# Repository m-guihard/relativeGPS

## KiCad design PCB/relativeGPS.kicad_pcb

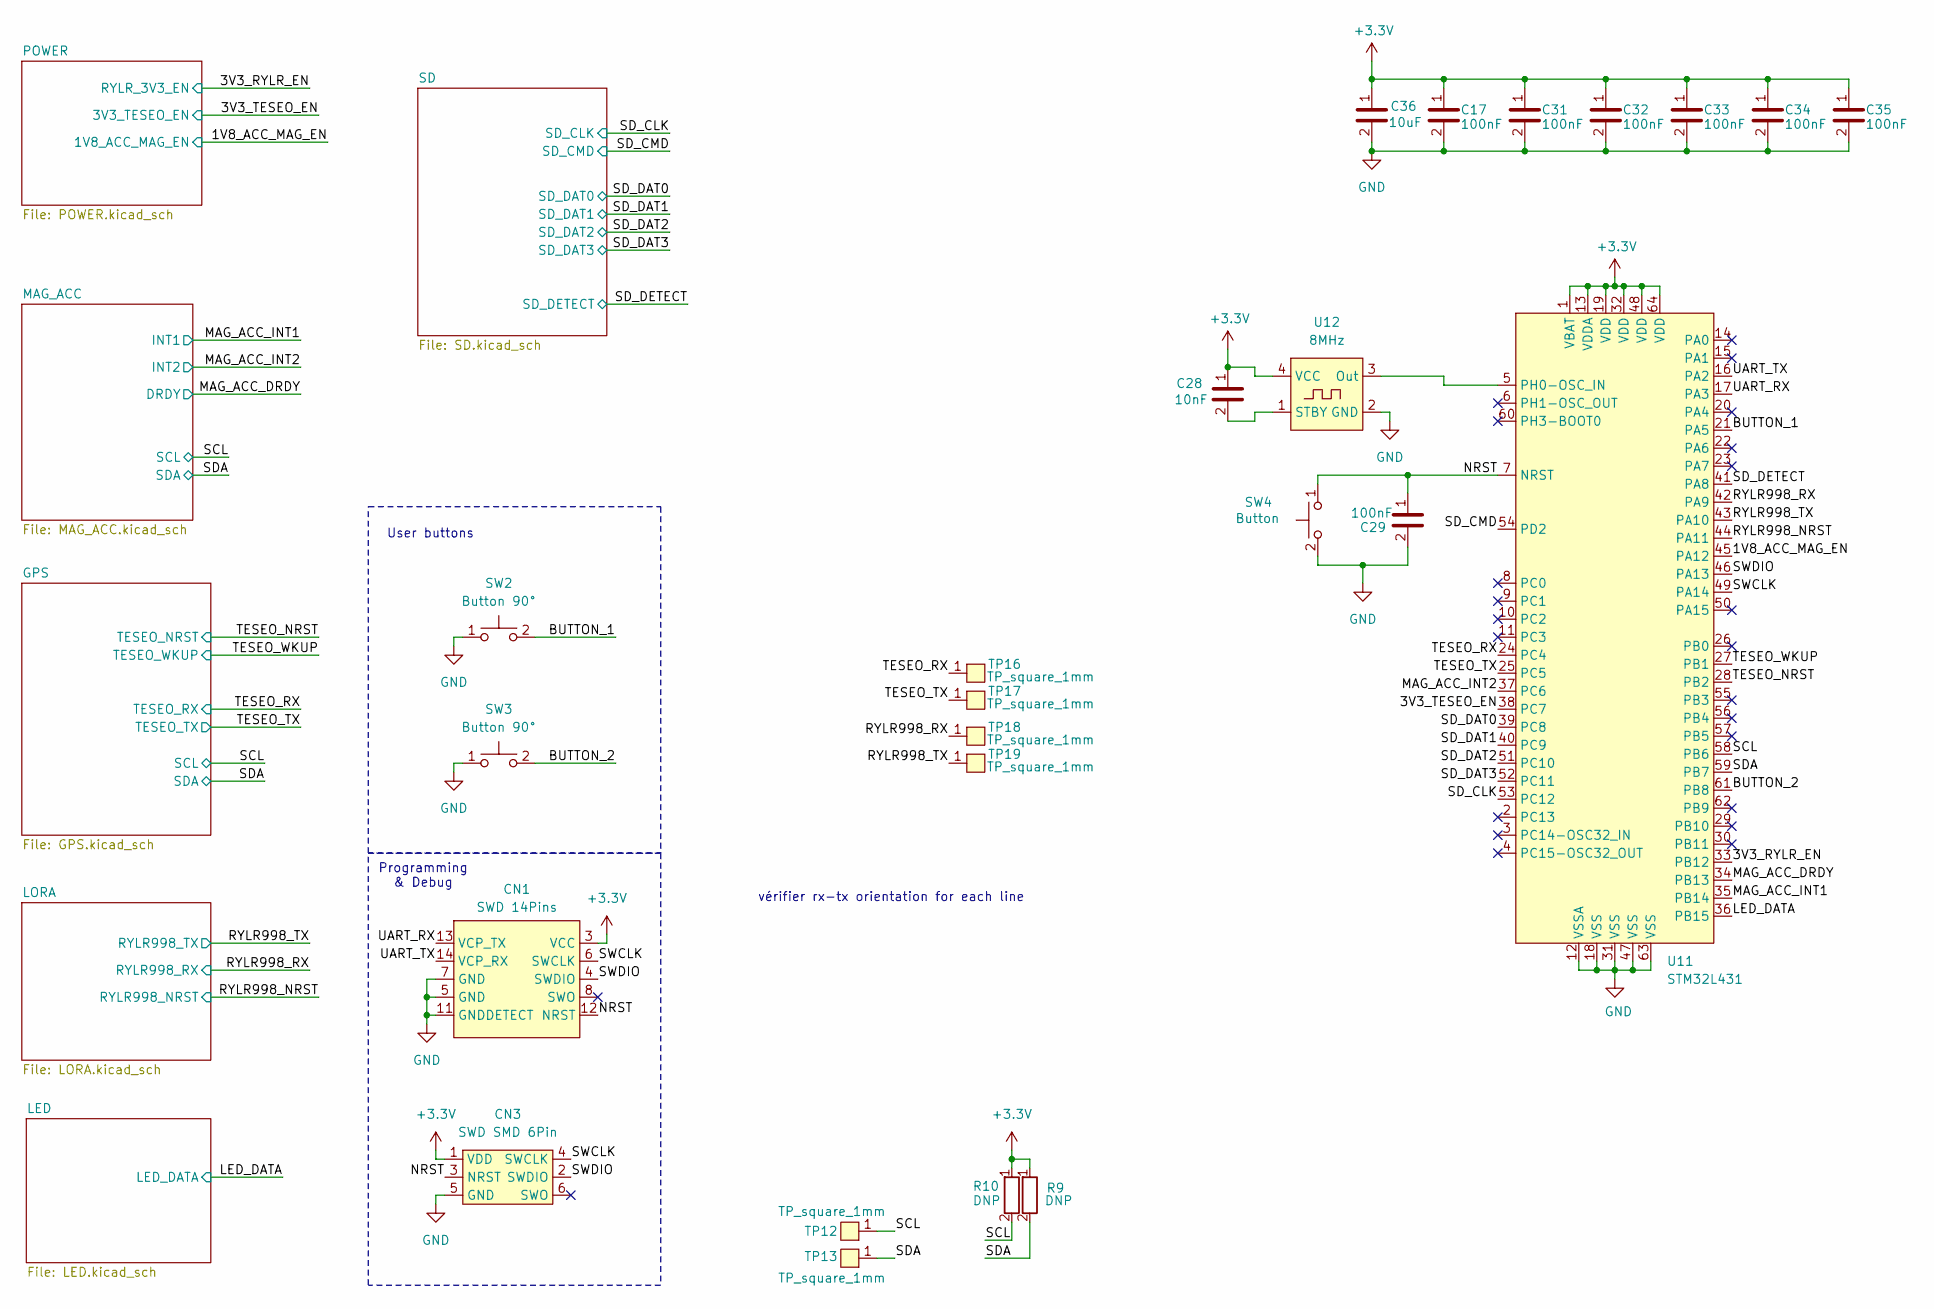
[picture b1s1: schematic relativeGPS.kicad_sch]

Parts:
C17, C29, C31, C32, C33, C34, C35: C_100nF_50V_10%_X7R_0402_H0.55; C_0402_H0.55; Manufacturer P/N GRM155R71H104KE14J; Digikey P/N 490-13342-1-ND
C28: C_10nF_50V_10%_X7R_0402_H0.55; C_0402_H0.55; Manufacturer P/N CGA2B3X7R1H103K050BE; Digikey P/N 445-173650-1-ND
C36: C_10uF_10V_20%_X5R_0402_H0.55; C_0402_H0.55; Manufacturer P/N GRM155R61A106ME11D; Digikey P/N 490-GRM155R61A106ME11DCT-ND
CN1: FTSH-107-01-L-DV-K-P-TR; Manufacturer P/N FTSH-107-01-L-DV-K-P-TR; Digikey P/N SAM13946CT-ND
CN3: TC2030-IDC; Debug_pads_6pin
R9, R10: R_DNP_0402; R_0402_H0.4
SW2, SW3: EVQ-P7A01P; Manufacturer P/N EVQ-P7A01P; Digikey P/N P16763CT-ND
SW4: TL3315NF160Q; Manufacturer P/N TL3315NF160Q; Digikey P/N EG4621CT-ND
TP12, TP13, TP16, TP17, TP18, TP19: TP_square_1mm; Testpoint_square_1mm
U11: STM32L431RCT6TR; LQFP-64_10x10mm_P0.5mm; Manufacturer P/N STM32L431RCT6TR; Digikey P/N 497-STM32L431RCT6CT-ND
U12: ASE-8.000MHZ-L-C-T; Manufacturer P/N ASE-8.000MHZ-L-C-T; Digikey P/N 535-ASE-8.000MHZ-L-C-TCT-ND

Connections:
+3.3V: C17.1, C28.1, C31.1, C32.1, C33.1, C34.1, C35.1, C36.1, CN1.3 (VCC), CN3.1 (VDD), R9.1, R10.1, U11.1 (VBAT), U11.13 (VDDA), U11.19 (VDD), U11.32 (VDD), U11.48 (VDD), U11.64 (VDD), U12.4 (VCC); also elsewhere on the board
/1V8_ACC_MAG_EN: U11.45 (PA12); also elsewhere on the board
/3V3_RYLR_EN: U11.33 (PB12); also elsewhere on the board
/3V3_TESEO_EN: U11.38 (PC7); also elsewhere on the board
/BUTTON_1: SW2.2, U11.21 (PA5)
/BUTTON_2: SW3.2, U11.61 (PB8)
/LED_DATA: U11.36 (PB15); also elsewhere on the board
/MAG_ACC_DRDY: U11.34 (PB13); also elsewhere on the board
/MAG_ACC_INT1: U11.35 (PB14); also elsewhere on the board
/MAG_ACC_INT2: U11.37 (PC6); also elsewhere on the board
/NRST: C29.1, CN1.12 (NRST), CN3.3 (NRST), SW4.1, U11.7 (NRST)
/RYLR998_NRST: U11.44 (PA11); also elsewhere on the board
/RYLR998_RX: TP18.1, U11.42 (PA9); also elsewhere on the board
/RYLR998_TX: TP19.1, U11.43 (PA10); also elsewhere on the board
/SCL: R10.2, TP12.1, U11.58 (PB6); also elsewhere on the board
/SDA: R9.2, TP13.1, U11.59 (PB7); also elsewhere on the board
/SD_CLK: U11.53 (PC12); also elsewhere on the board
/SD_CMD: U11.54 (PD2); also elsewhere on the board
/SD_DAT0: U11.39 (PC8); also elsewhere on the board
/SD_DAT1: U11.40 (PC9); also elsewhere on the board
/SD_DAT2: U11.51 (PC10); also elsewhere on the board
/SD_DAT3: U11.52 (PC11); also elsewhere on the board
/SD_DETECT: U11.41 (PA8); also elsewhere on the board
/SWCLK: CN1.6 (SWCLK), CN3.4 (SWCLK), U11.49 (PA14)
/SWDIO: CN1.4 (SWDIO), CN3.2 (SWDIO), U11.46 (PA13)
/TESEO_NRST: U11.28 (PB2); also elsewhere on the board
/TESEO_RX: TP16.1, U11.24 (PC4); also elsewhere on the board
/TESEO_TX: TP17.1, U11.25 (PC5); also elsewhere on the board
/TESEO_WKUP: U11.27 (PB1); also elsewhere on the board
/UART_RX: CN1.13 (VCP_TX), U11.17 (PA3)
/UART_TX: CN1.14 (VCP_RX), U11.16 (PA2)
GND: C17.2, C29.2, C31.2, C32.2, C33.2, C34.2, C35.2, C36.2, CN1.5 (GND), CN1.7 (GND), CN1.11 (GNDDETECT), CN3.5 (GND), SW2.1, SW3.1, SW4.2, U11.12 (VSSA), U11.18 (VSS), U11.31 (VSS), U11.47 (VSS), U11.63 (VSS), U12.2 (GND); also elsewhere on the board
unnamed: U11.5 (PH0-OSC_IN), U12.3 (Out)
unnamed: C28.2, U12.1 (STBY)

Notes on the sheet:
Programming & Debug
vérifier rx-tx orientation for each line
User buttons

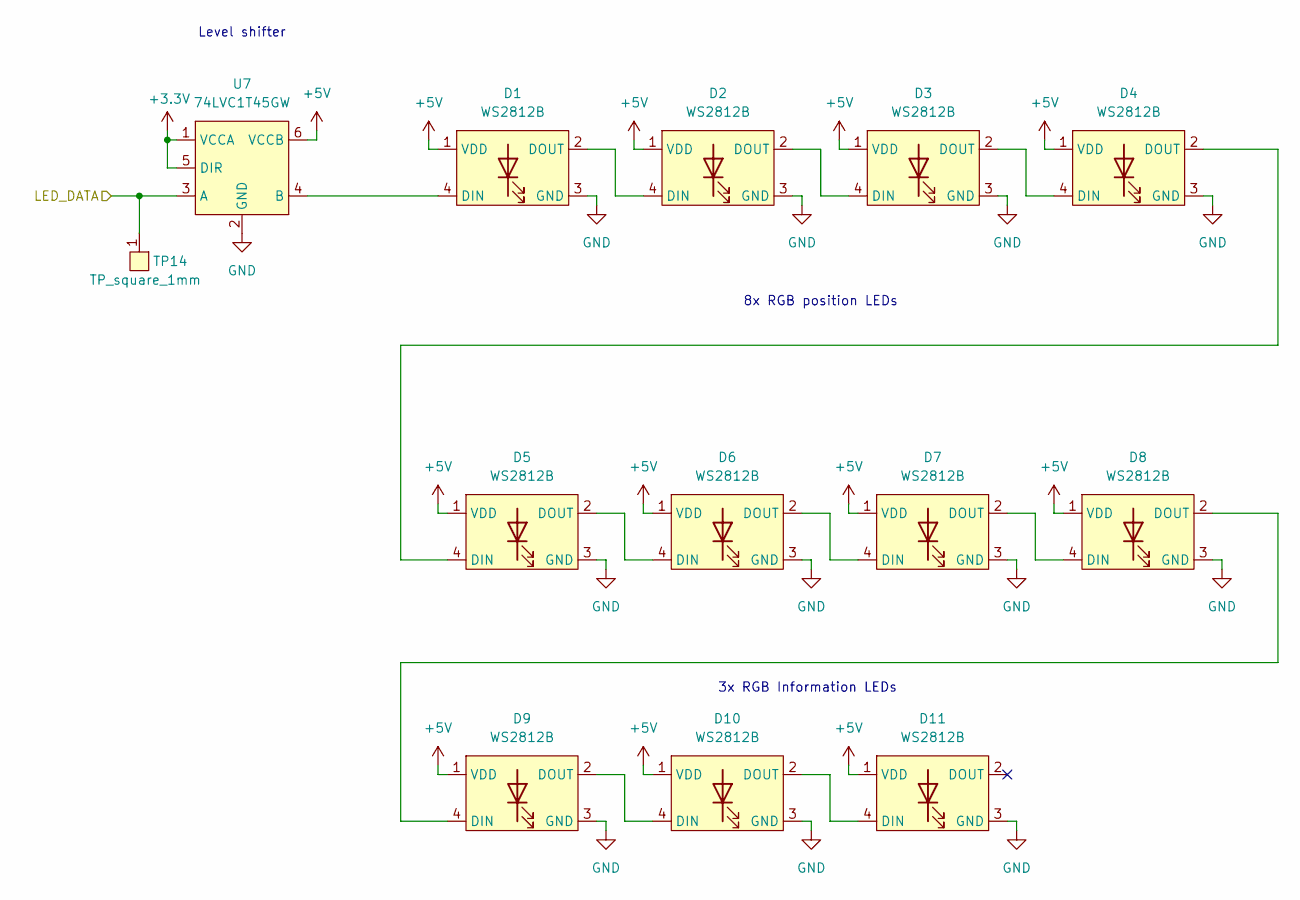
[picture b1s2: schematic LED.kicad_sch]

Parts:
D1, D2, D3, D4, D5, D6, D7, D8, D9, D10, D11: COM-16347; Manufacturer P/N COM-16347; Digikey P/N 1568-COM-16347CT-ND
TP14: TP_square_1mm; Testpoint_square_1mm
U7: 74LVC1T45GW.125; TSSOP6_SOT363-2; Manufacturer P/N 74LVC1T45GW.125; Digikey P/N 1727-4560-1-ND

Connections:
+3.3V: U7.1 (VCCA), U7.5 (DIR); also elsewhere on the board
+5V: D1.1 (VDD), D2.1 (VDD), D3.1 (VDD), D4.1 (VDD), D5.1 (VDD), D6.1 (VDD), D7.1 (VDD), D8.1 (VDD), D9.1 (VDD), D10.1 (VDD), D11.1 (VDD), U7.6 (VCCB); also elsewhere on the board
/LED_DATA: TP14.1, U7.3 (A); also elsewhere on the board
GND: D1.3 (GND), D2.3 (GND), D3.3 (GND), D4.3 (GND), D5.3 (GND), D6.3 (GND), D7.3 (GND), D8.3 (GND), D9.3 (GND), D10.3 (GND), D11.3 (GND), U7.2 (GND); also elsewhere on the board
unnamed: D1.4 (DIN), U7.4 (B)
unnamed: D1.2 (DOUT), D2.4 (DIN)
unnamed: D2.2 (DOUT), D3.4 (DIN)
unnamed: D3.2 (DOUT), D4.4 (DIN)
unnamed: D4.2 (DOUT), D5.4 (DIN)
unnamed: D5.2 (DOUT), D6.4 (DIN)
unnamed: D6.2 (DOUT), D7.4 (DIN)
unnamed: D7.2 (DOUT), D8.4 (DIN)
unnamed: D8.2 (DOUT), D9.4 (DIN)
unnamed: D9.2 (DOUT), D10.4 (DIN)
unnamed: D10.2 (DOUT), D11.4 (DIN)

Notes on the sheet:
3x RGB Information LEDs
Level shifter
8x RGB position LEDs

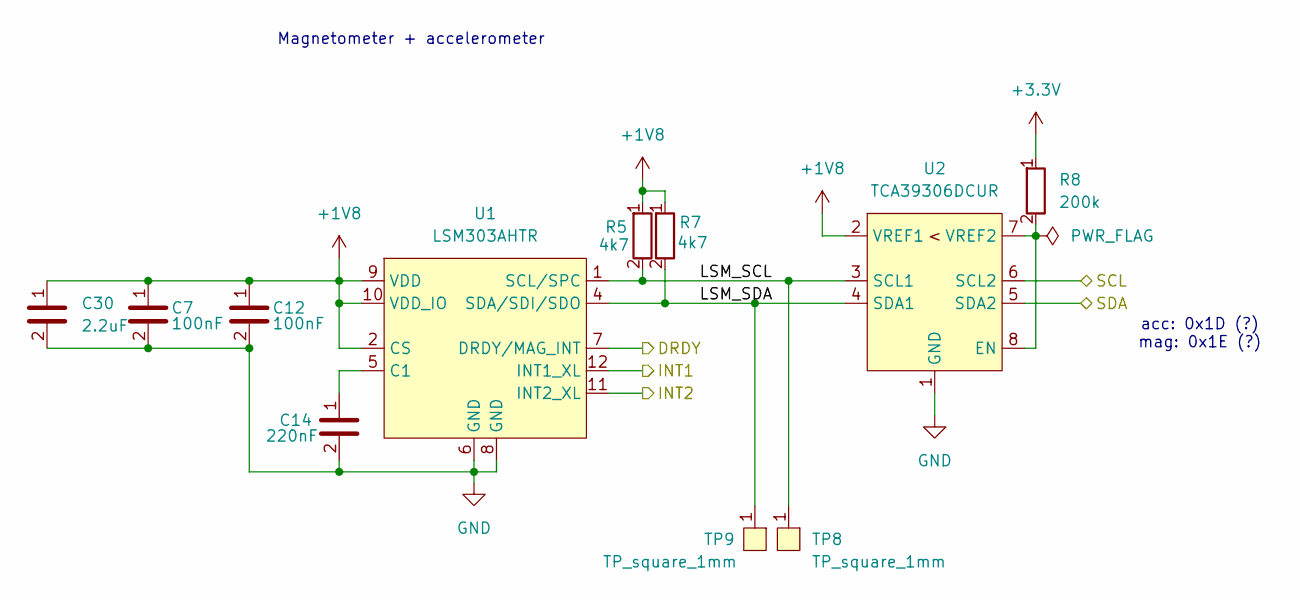
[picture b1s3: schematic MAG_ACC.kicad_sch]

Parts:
C7, C12: C_100nF_50V_10%_X7R_0402_H0.55; C_0402_H0.55; Manufacturer P/N GRM155R71H104KE14J; Digikey P/N 490-13342-1-ND
C14: C_220nF_16V_10%_X7R_0402_H0.55; C_0402_H0.55; Manufacturer P/N GCM155R71C224KE02D; Digikey P/N 490-10671-1-ND
C30: C_2.2uF_25V_25%_X5R_0402_H0.55; C_0402_H0.55; Manufacturer P/N GRM155R61E225ME15D; Digikey P/N 490-10457-1-ND
R5, R7: R_4k7_5%_1/16W_0402; R_0402_H0.4; Manufacturer P/N RC0402JR-074K7P; Digikey P/N YAG1287CT-ND
R8: R_200k_1%_1/16W_0402; R_0402_H0.4; Manufacturer P/N RC0402FR-13200KL; Digikey P/N 13-RC0402FR-13200KLCT-ND
TP8, TP9: TP_square_1mm; Testpoint_square_1mm
U1: LSM303AH; LSM303AHTR; Manufacturer P/N LSM303AHTR; Digikey P/N 497-17053-1-ND
U2: TCA39306DCUR; Manufacturer P/N TCA39306DCUR; Digikey P/N 296-TCA39306DCURCT-ND

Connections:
+1V8: C7.1, C12.1, C30.1, R5.1, R7.1, U1.2 (CS), U1.9 (VDD), U1.10 (VDD_IO), U2.2 (VREF1); also elsewhere on the board
+3.3V: R8.1; also elsewhere on the board
/MAG_ACC/LSM_SCL: R5.2, TP8.1, U1.1 (SCL/SPC), U2.3 (SCL1)
/MAG_ACC/LSM_SDA: R7.2, TP9.1, U1.4 (SDA/SDI/SDO), U2.4 (SDA1)
/MAG_ACC_DRDY: U1.7 (DRDY/MAG_INT); also elsewhere on the board
/MAG_ACC_INT1: U1.12 (INT1_XL); also elsewhere on the board
/MAG_ACC_INT2: U1.11 (INT2_XL); also elsewhere on the board
/SCL: U2.6 (SCL2); also elsewhere on the board
/SDA: U2.5 (SDA2); also elsewhere on the board
GND: C7.2, C12.2, C14.2, C30.2, U1.6 (GND), U1.8 (GND), U2.1 (GND); also elsewhere on the board
unnamed: C14.1, U1.5 (C1)
unnamed: R8.2, U2.7 (VREF2), U2.8 (EN)

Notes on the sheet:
Magnetometer + accelerometer
acc: 0x1D (?) mag: 0x1E (?)

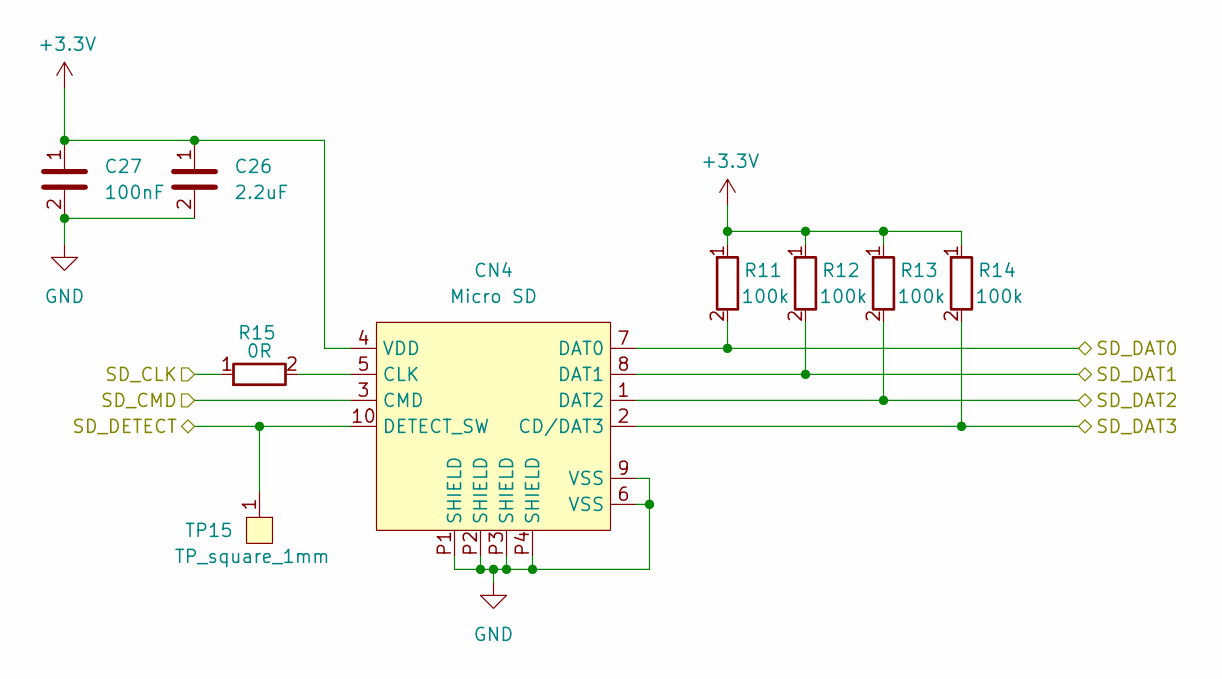
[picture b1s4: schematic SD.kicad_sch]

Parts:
C26: C_2.2uF_25V_25%_X5R_0402_H0.55; C_0402_H0.55; Manufacturer P/N GRM155R61E225ME15D; Digikey P/N 490-10457-1-ND
C27: C_100nF_50V_10%_X7R_0402_H0.55; C_0402_H0.55; Manufacturer P/N GRM155R71H104KE14J; Digikey P/N 490-13342-1-ND
CN4: 5033981892; Micro_SD_5033981892; Manufacturer P/N 5033981892; Digikey P/N WM11190CT-ND
R11, R12, R13, R14: R_100k_1%_1/16W_0402; R_0402_H0.4; Manufacturer P/N RC0402FR-07100KL; Digikey P/N 311-100KLRCT-ND
R15: R_0R_1%_1/16W_0402; R_0402_H0.4; Manufacturer P/N AC0402FR-070RL; Digikey P/N 13-AC0402FR-070RLCT-ND
TP15: TP_square_1mm; Testpoint_square_1mm

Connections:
+3.3V: C26.1, C27.1, CN4.4 (VDD), R11.1, R12.1, R13.1, R14.1; also elsewhere on the board
/SD_CLK: R15.1; also elsewhere on the board
/SD_CMD: CN4.3 (CMD); also elsewhere on the board
/SD_DAT0: CN4.7 (DAT0), R11.2; also elsewhere on the board
/SD_DAT1: CN4.8 (DAT1), R12.2; also elsewhere on the board
/SD_DAT2: CN4.1 (DAT2), R13.2; also elsewhere on the board
/SD_DAT3: CN4.2 (CD/DAT3), R14.2; also elsewhere on the board
/SD_DETECT: CN4.10 (DETECT_SW), TP15.1; also elsewhere on the board
GND: C26.2, C27.2, CN4.6 (VSS), CN4.9 (VSS), CN4.P1 (SHIELD), CN4.P2 (SHIELD), CN4.P3 (SHIELD), CN4.P4 (SHIELD); also elsewhere on the board
unnamed: CN4.5 (CLK), R15.2

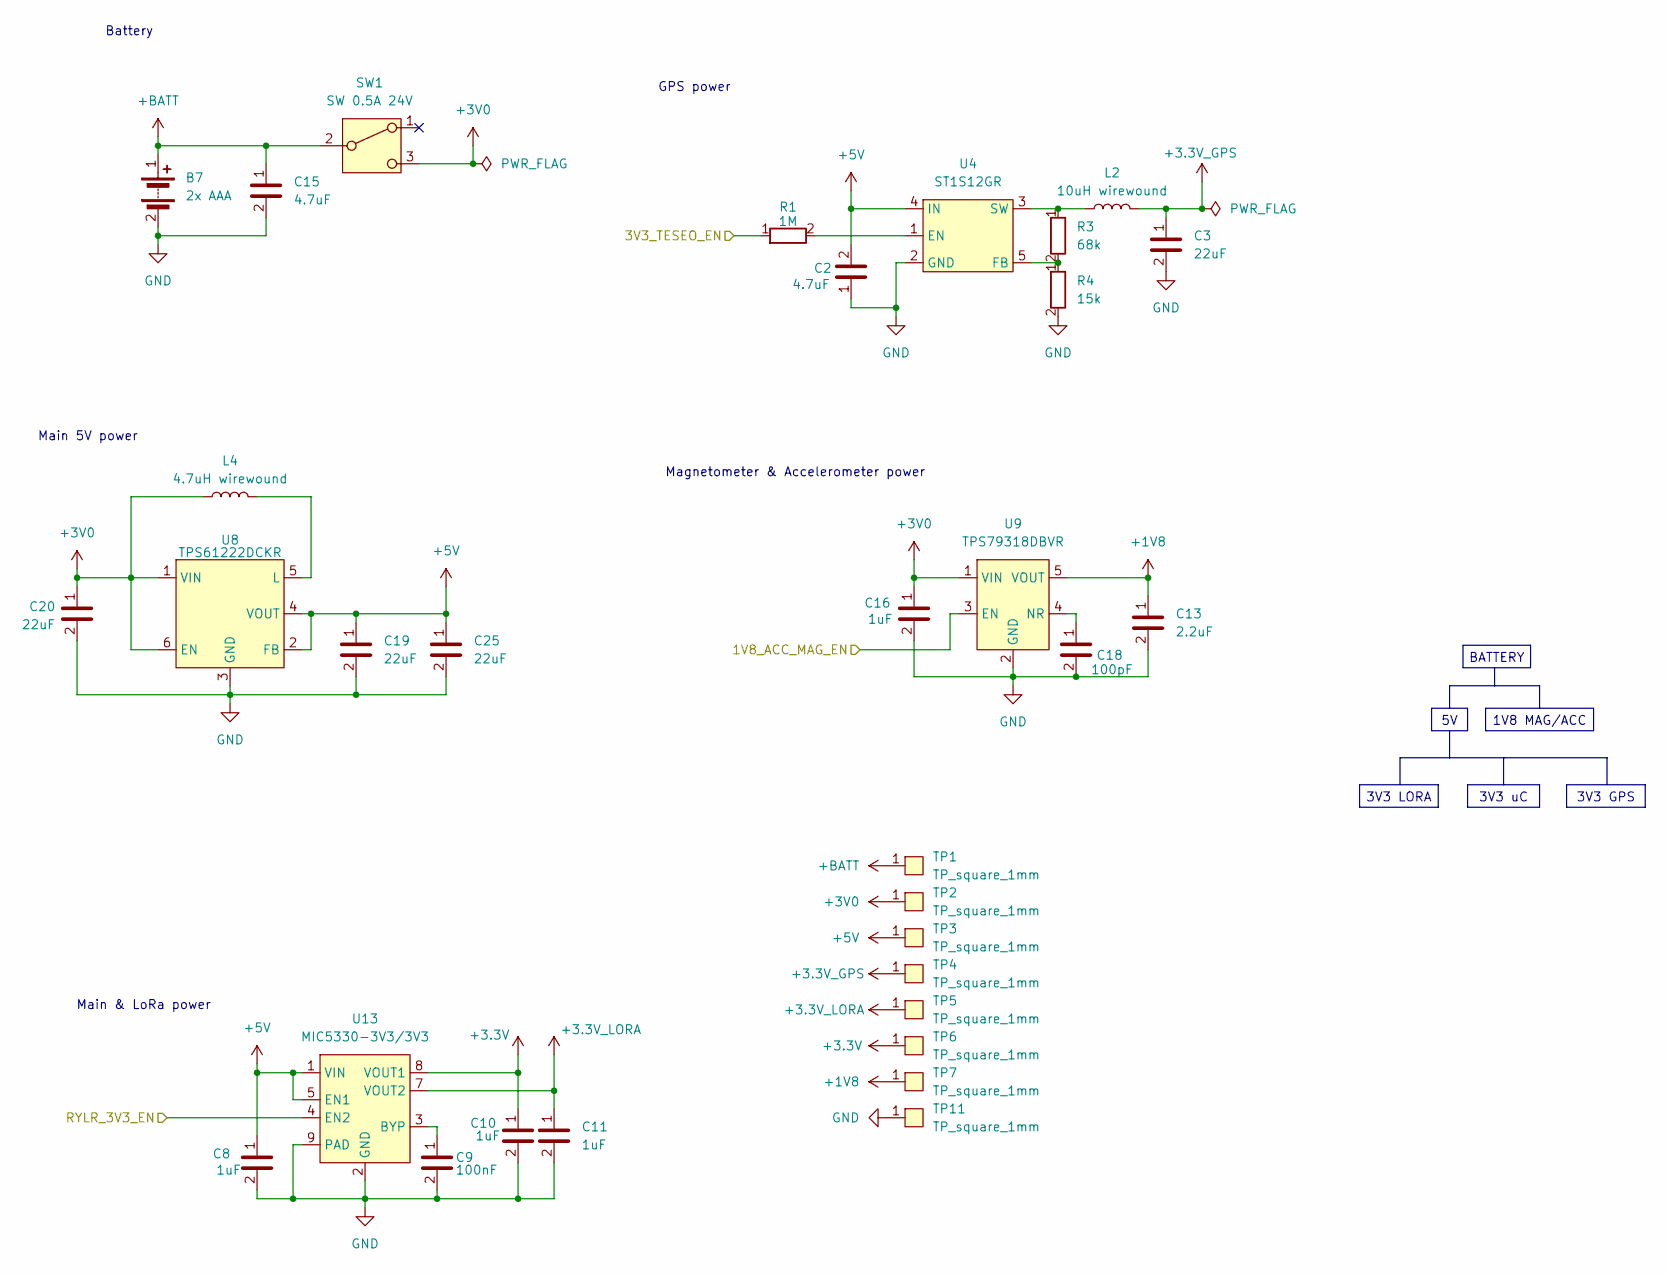
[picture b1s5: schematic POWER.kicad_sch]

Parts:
B7: AAA_2X_Holder; Manufacturer P/N 2468; Digikey P/N 36-2468-ND
C2, C15: C_4.7uF_10V_10%_X7S_0603_H0.95; C_0603_H0.95; Manufacturer P/N GRM188C71A475KE11D; Digikey P/N 490-11992-1-ND
C3: C_22uF_6.3V_20%_X5R_0805_H1.4; C_0805_H1.4; Manufacturer P/N C0805C226M9PAC7800; Digikey P/N 399-C0805C226M9PAC7800CT-ND
C8, C10, C11: C_1uF_50V_10%_X5R_0402_H0.55; C_0402_H0.55; Manufacturer P/N GRM155R61H105KE05D; Digikey P/N 490-GRM155R61H105KE05DCT-ND
C9: C_100nF_50V_10%_X7R_0402_H0.55; C_0402_H0.55; Manufacturer P/N GRM155R71H104KE14J; Digikey P/N 490-13342-1-ND
C13: C_2.2uF_25V_25%_X5R_0402_H0.55; C_0402_H0.55; Manufacturer P/N GRM155R61E225ME15D; Digikey P/N 490-10457-1-ND
C16: C_1uF_50V_10%_X5R_0603_H0.9; C_0603_H0.95; Manufacturer P/N GRT188R61H105KE13D; Digikey P/N 490-12330-1-ND
C18: C_100pF_50V_5%_C0G_0603_H0.9; C_0603_H0.95; Manufacturer P/N GRM1885C1H101JA01D; Digikey P/N 490-1427-1-ND
C19, C20, C25: C_22uF_25V_20%_X5S_0603_H1; C_0603_H0.95; Manufacturer P/N GRM188C61E226ME01J; Digikey P/N 490-GRM188C61E226ME01JCT-ND
L2: L_10uH_20%_1.51A_160mOhm; LTF5022T-100M1R3-D; Manufacturer P/N LTF5022T-100M1R3-D; Digikey P/N 445-16215-1-ND
L4: L_4.7uH_20%_1.7A_120mOhm; LQH3NPZ4R7MMEL; Manufacturer P/N LQH3NPZ4R7MMEL; Digikey P/N 490-LQH3NPZ4R7MMELCT-ND
R1: R_1M_5%_1/16W_0402; R_0402_H0.4; Manufacturer P/N RC0402JR-071ML; Digikey P/N 311-1.0MJRCT-ND
R3: R_68k_1%_1/16W_0402; R_0402_H0.4; Manufacturer P/N AC0402FR-0768KL; Digikey P/N YAG3506CT-ND
R4: R_15k_1%_1/16W_0402; R_0402_H0.4; Manufacturer P/N RC0402FR-1315KL; Digikey P/N 13-RC0402FR-1315KLCT-ND
SW1: switch_slide_2pos; 09.10290.01; Manufacturer P/N 09.10290.01; Digikey P/N 1948-1089-ND
TP1, TP2, TP3, TP4, TP5, TP6, TP7, TP11: TP_square_1mm; Testpoint_square_1mm
U4: ST1S12GR; Manufacturer P/N ST1S12GR; Digikey P/N 497-6906-1-ND
U8: TPS61222DCKR; Manufacturer P/N TPS61222DCKR; Digikey P/N 296-39435-1-ND
U9: TPS79318DBVR; Manufacturer P/N TPS79318DBVR; Digikey P/N 296-12155-1-ND
U13: MIC5330-SSYML-TR; MIC5330; Manufacturer P/N MIC5330-SSYML-TR; Digikey P/N 576-1947-1-ND

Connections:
+1V8: C13.1, TP7.1, U9.5 (VOUT); also elsewhere on the board
+3.3V: C10.1, TP6.1, U13.8 (VOUT1); also elsewhere on the board
+3.3V_GPS: C3.1, L2.2, TP4.1; also elsewhere on the board
+3.3V_LORA: C11.1, TP5.1, U13.7 (VOUT2); also elsewhere on the board
+3V0: C16.1, C20.1, L4.1, SW1.3, TP2.1, U8.1 (VIN), U8.6 (EN), U9.1 (VIN)
+5V: C2.2, C8.1, C19.1, C25.1, TP3.1, U4.4 (IN), U8.2 (FB), U8.4 (VOUT), U13.1 (VIN), U13.5 (EN1); also elsewhere on the board
+BATT: B7.1, C15.1, SW1.2, TP1.1
/1V8_ACC_MAG_EN: U9.3 (EN); also elsewhere on the board
/3V3_RYLR_EN: U13.4 (EN2); also elsewhere on the board
/3V3_TESEO_EN: R1.1; also elsewhere on the board
GND: B7.2, C2.1, C3.2, C8.2, C9.2, C10.2, C11.2, C13.2, C15.2, C16.2, C18.2, C19.2, C20.2, C25.2, R4.2, TP11.1, U4.2 (GND), U8.3 (GND), U9.2 (GND), U13.2 (GND), U13.9 (PAD); also elsewhere on the board
unnamed: R1.2, U4.1 (EN)
unnamed: R3.2, R4.1, U4.5 (FB)
unnamed: L2.1, R3.1, U4.3 (SW)
unnamed: L4.2, U8.5 (L)
unnamed: C18.1, U9.4 (NR)
unnamed: C9.1, U13.3 (BYP)

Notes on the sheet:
Magnetometer & Accelerometer power
Main & LoRa power
Main 5V power
GPS power
Battery
3V3 LORA
3V3 uC
BATTERY
1V8 MAG/ACC
3V3 GPS

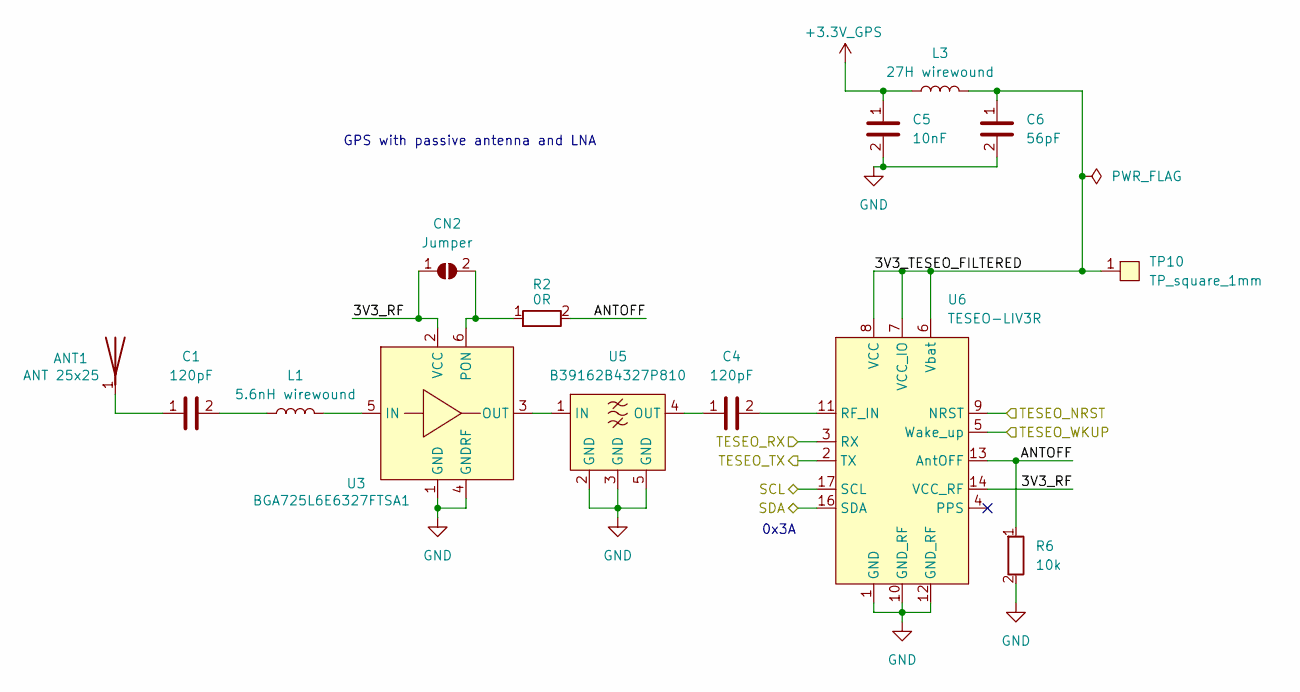
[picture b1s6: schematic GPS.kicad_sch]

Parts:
ANT1: ANT2525B00DT1516S; Manufacturer P/N ANT2525B00DT1516S; Digikey P/N 311-1539-ND
C1, C4: C_120pF_50V_5%_C0G_0402_H0.55; C_0402_H0.55; Manufacturer P/N GCM1555C1H121JA16D; Digikey P/N 490-13287-1-ND
C5: C_10nF_50V_10%_X7R_0402_H0.55; C_0402_H0.55; Manufacturer P/N CGA2B3X7R1H103K050BE; Digikey P/N 445-173650-1-ND
C6: C_56pF_50V_2%_C0G_0201_H0.33; C_0402_H0.55; Manufacturer P/N GRM0335C1H560GA01D; Digikey P/N 490-13329-1-ND
CN2: Solder_Jumper-2_Open; SolderJumper-2_Open
L1: L_5.6nH_2%_1.77A_40mOhm; LQW15AN5N6G80D; Manufacturer P/N LQW15AN5N6G80D; Digikey P/N 490-LQW15AN5N6G80DCT-ND
L3: L_27nH_5%_0.35A_460mOhm; LQG15HS27NJ02D; Manufacturer P/N LQG15HS27NJ02D; Digikey P/N 490-2628-1-ND
R2: R_0R_0603; R_0603_H0.55; Manufacturer P/N RC0603JR-070RL; Digikey P/N 311-0.0GRCT-ND
R6: R_10k_5%_1/16W_0402; R_0402_H0.4; Manufacturer P/N RC0402JR-0710KP; Digikey P/N YAG1281CT-ND
TP10: TP_square_1mm; Testpoint_square_1mm
U3: BGA725L6E6327FTSA1; Manufacturer P/N BGA725L6E6327FTSA1; Digikey P/N BGA725L6E6327FTSA1CT-ND
U5: B39162B4327P810; Manufacturer P/N B39162B4327P810; Digikey P/N 495-7424-1-ND
U6: TESEO-LIV3R; Manufacturer P/N TESEO-LIV3R; Digikey P/N 497-19468-1-ND

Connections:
+3.3V_GPS: C5.1, L3.1; also elsewhere on the board
/GPS/3V3_RF: CN2.1, U3.2 (VCC), U6.14 (VCC_RF)
/GPS/3V3_TESEO_FILTERED: C6.1, L3.2, TP10.1, U6.6 (Vbat), U6.7 (VCC_IO), U6.8 (VCC)
/GPS/ANTOFF: R2.2, R6.1, U6.13 (AntOFF)
/SCL: U6.17 (SCL); also elsewhere on the board
/SDA: U6.16 (SDA); also elsewhere on the board
/TESEO_NRST: U6.9 (NRST); also elsewhere on the board
/TESEO_RX: U6.3 (RX); also elsewhere on the board
/TESEO_TX: U6.2 (TX); also elsewhere on the board
/TESEO_WKUP: U6.5 (Wake_up); also elsewhere on the board
GND: C5.2, C6.2, R6.2, U3.1 (GND), U3.4 (GNDRF), U5.2 (GND), U5.3 (GND), U5.5 (GND), U6.1 (GND), U6.10 (GND_RF), U6.12 (GND_RF); also elsewhere on the board
unnamed: ANT1.1, C1.1
unnamed: C1.2, L1.1
unnamed: L1.2, U3.5 (IN)
unnamed: U3.3 (OUT), U5.1 (IN)
unnamed: CN2.2, R2.1, U3.6 (PON)
unnamed: C4.1, U5.4 (OUT)
unnamed: C4.2, U6.11 (RF_IN)

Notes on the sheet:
GPS with passive antenna and LNA
0x3A

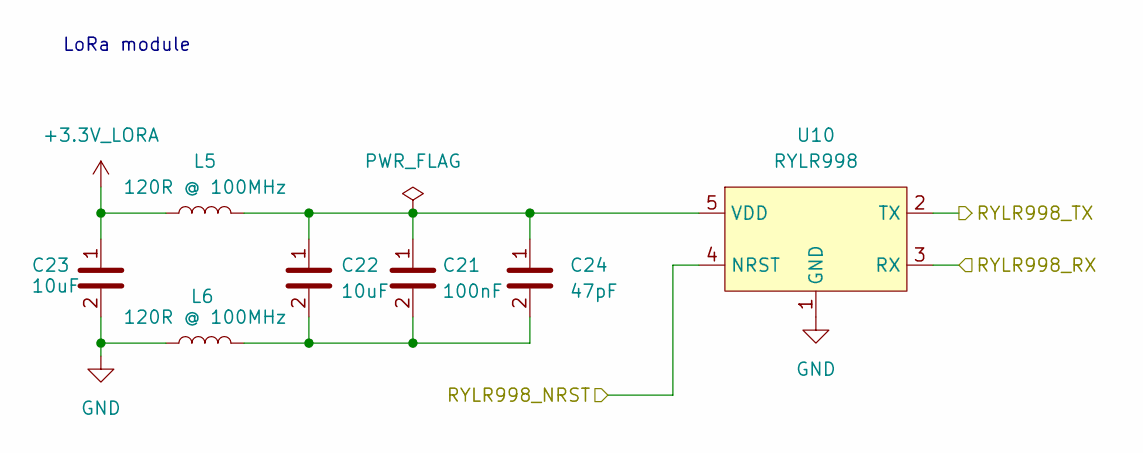
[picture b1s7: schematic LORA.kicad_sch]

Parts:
C21: C_100nF_50V_10%_X7R_0402_H0.55; C_0402_H0.55; Manufacturer P/N GRM155R71H104KE14J; Digikey P/N 490-13342-1-ND
C22, C23: C_10uF_10V_20%_X5R_0603H0.9; C_0603_H0.95; Manufacturer P/N GRM188R61A106ME69D; Digikey P/N 490-10475-1-ND
C24: C_47pF_50V_5%_C0G_0402; C_0402_H0.55; Manufacturer P/N GRM1555C1H470JA01D; Digikey P/N 490-5942-1-ND
L5, L6: FERR_120R@100MHz_5%_1.5A_95mOhm; FERR_0402_H0.55; Manufacturer P/N BLM15EG121SN1D; Digikey P/N 490-4004-1-ND
U10: RYLR998; RYLR998_flat; Manufacturer P/N RYLR998

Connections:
+3.3V_LORA: C23.1, L5.1; also elsewhere on the board
/RYLR998_NRST: U10.4 (NRST); also elsewhere on the board
/RYLR998_RX: U10.3 (RX); also elsewhere on the board
/RYLR998_TX: U10.2 (TX); also elsewhere on the board
GND: C23.2, L6.1, U10.1 (GND); also elsewhere on the board
unnamed: C21.2, C22.2, C24.2, L6.2
unnamed: C21.1, C22.1, C24.1, L5.2, U10.5 (VDD)

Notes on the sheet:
LoRa module

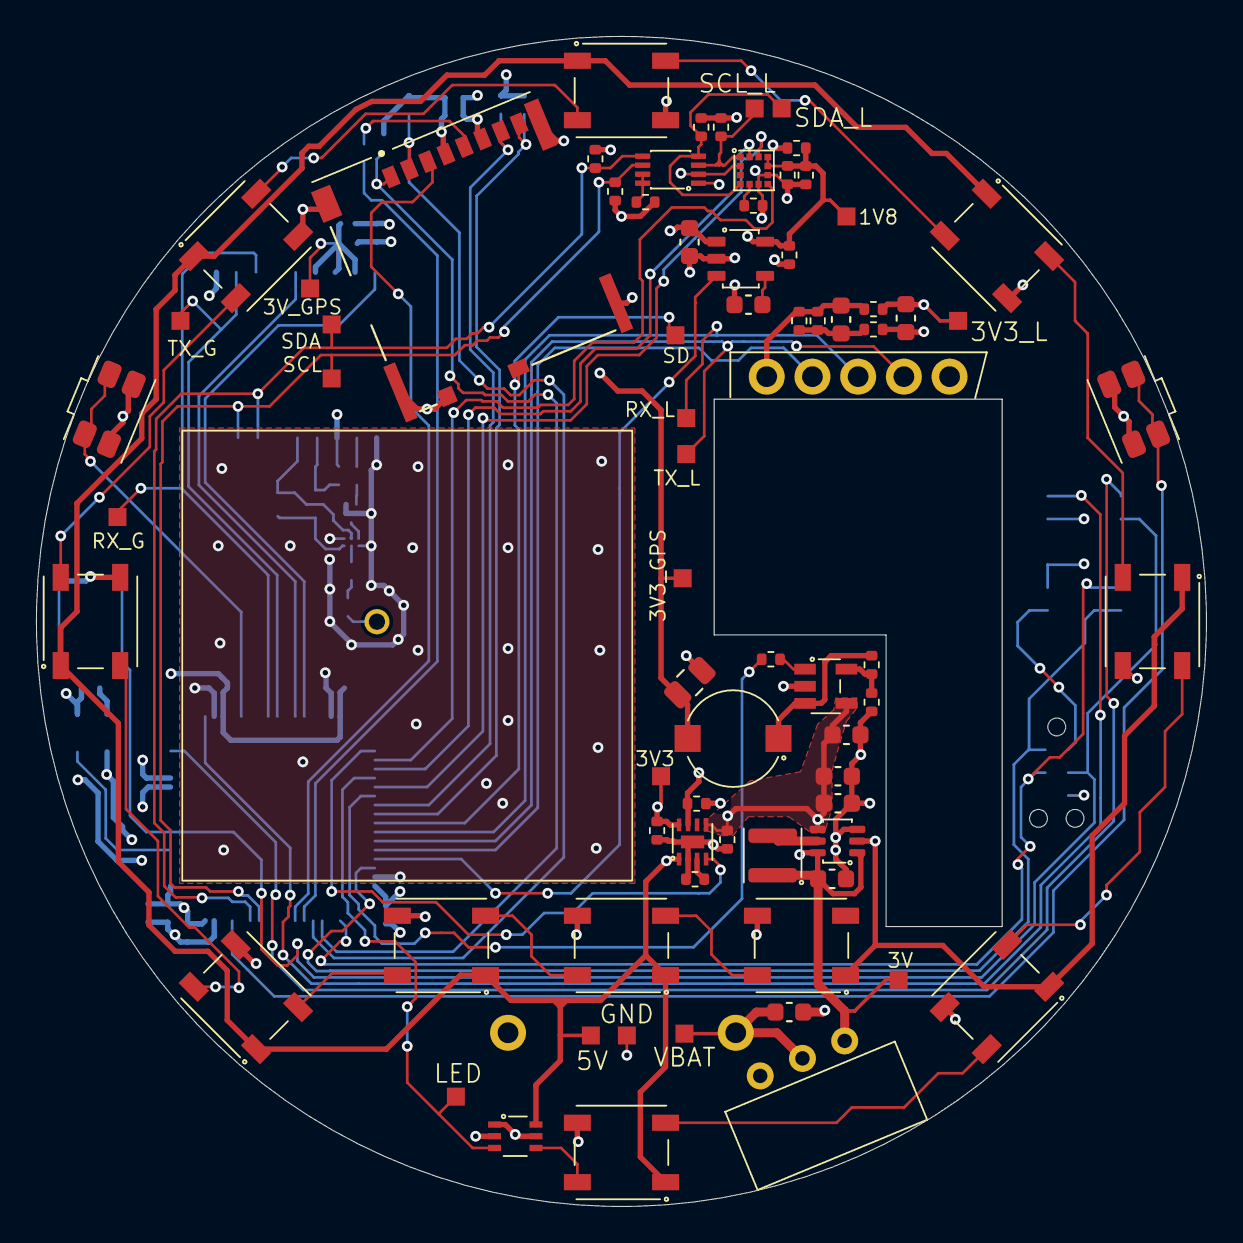
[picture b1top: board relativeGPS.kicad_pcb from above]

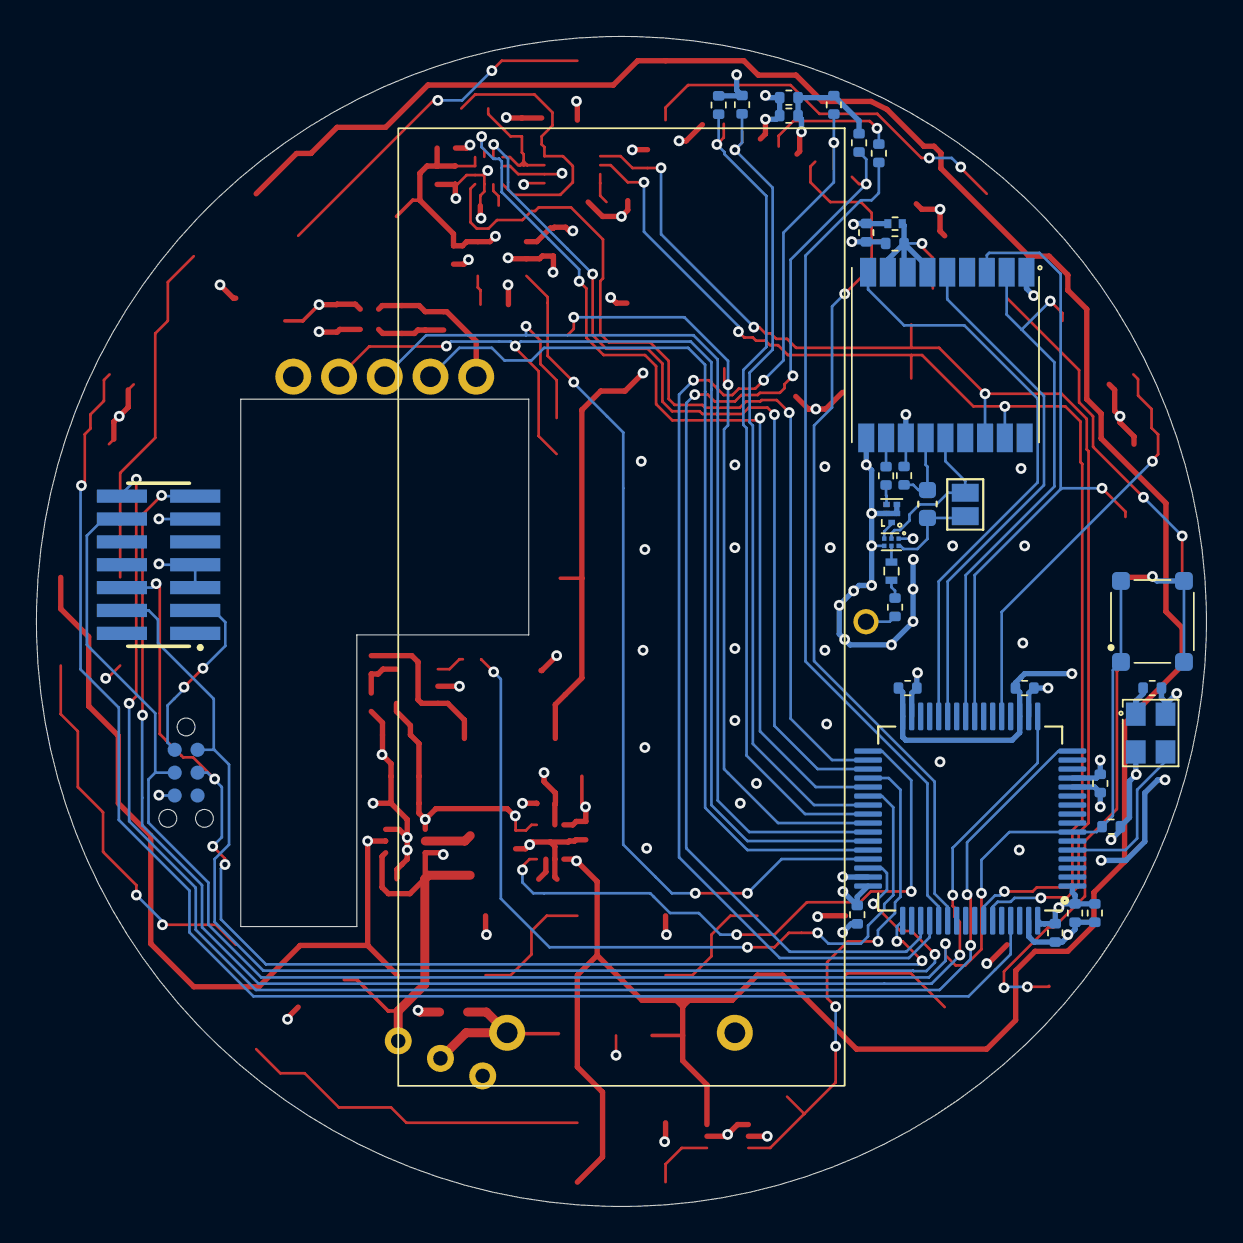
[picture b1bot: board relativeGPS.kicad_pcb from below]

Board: 4 copper layers, 65.0 x 65.0 mm, 110 parts (34 on the bottom side), 74 nets.

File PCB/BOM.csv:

Reference,Value,Qty,Digikey P/N,Price,Value Disp
ANT1,ANT2525B00DT1516S,1,311-1539-ND,2.48,ANT 25x25
B7,AAA_2X_Holder,1,36-2468-ND,1.17,2x AAA
C1/C4,C_120pF_50V_5%_C0G_0402_H0.55,2,490-13287-1-ND,0.09,120pF
C2/C15,C_4.7uF_10V_10%_X7S_0603_H0.95,2,490-11992-1-ND,0.21,4.7uF
C3,C_22uF_6.3V_20%_X5R_0805_H1.4,1,399-C0805C226M9PAC7800CT-ND,0.19,22uF
C5/C28,C_10nF_50V_10%_X7R_0402_H0.55,2,445-173650-1-ND,0.15,10nF
C6,C_56pF_50V_2%_C0G_0201_H0.33,1,490-13329-1-ND,0.09,56pF
C7/C9/C12/C17/C21/C27/C29/C31/C32/C33/C34/C35,C_100nF_50V_10%_X7R_0402_H0.55,12,490-13342-1-ND,0.09,100nF
C8/C10/C11,C_1uF_50V_10%_X5R_0402_H0.55,3,490-GRM155R61H105KE05DCT-ND,0.07,1uF
C13/C26/C30,C_2.2uF_25V_25%_X5R_0402_H0.55,3,490-10457-1-ND,0.17,2.2uF
C14,C_220nF_16V_10%_X7R_0402_H0.55,1,490-10671-1-ND,0.09,220nF
C16,C_1uF_50V_10%_X5R_0603_H0.9,1,490-12330-1-ND,0.16,1uF
C18,C_100pF_50V_5%_C0G_0603_H0.9,1,490-1427-1-ND,0.09,100pF
C19/C20/C25,C_22uF_25V_20%_X5S_0603_H1,3,490-GRM188C61E226ME01JCT-ND,0.41,22uF
C22/C23,C_10uF_10V_20%_X5R_0603H0.9,2,490-10475-1-ND,0.13,10uF
C24,C_47pF_50V_5%_C0G_0402,1,490-5942-1-ND,0.09,47pF
C36,C_10uF_10V_20%_X5R_0402_H0.55,1,490-GRM155R61A106ME11DCT-ND,0.09,10uF
CN1,FTSH-107-01-L-DV-K-P-TR,1,SAM13946CT-ND,2.72,SWD 14Pins
CN2,Solder_Jumper-2_Open,1,,,Jumper
CN3,TC2030-IDC,1,-,-,SWD SMD 6Pin
CN4,5033981892,1,WM11190CT-ND,2.55,Micro SD
D1/D2/D3/D4/D5/D6/D7/D8/D9/D10/D11,COM-16347,11,1568-COM-16347CT-ND,0.5,WS2812B
L1,L_5.6nH_2%_1.77A_40mOhm,1,490-LQW15AN5N6G80DCT-ND,0.2,5.6nH wirewound
L2,L_10uH_20%_1.51A_160mOhm,1,445-16215-1-ND,1.4,10uH wirewound
L3,L_27nH_5%_0.35A_460mOhm,1,490-2628-1-ND,0.09,27H wirewound
L4,L_4.7uH_20%_1.7A_120mOhm,1,490-LQH3NPZ4R7MMELCT-ND,0.32,4.7uH wirewound
L5/L6,FERR_120R@100MHz_5%_1.5A_95mOhm,2,490-4004-1-ND,0.15,120R @ 100MHz
R1,R_1M_5%_1/16W_0402,1,311-1.0MJRCT-ND,0.09,1M
R2,R_0R_0603,1,311-0.0GRCT-ND,0.09,0R
R3,R_68k_1%_1/16W_0402,1,YAG3506CT-ND,0.09,68k
R4,R_15k_1%_1/16W_0402,1,13-RC0402FR-1315KLCT-ND,0.09,15k
R5/R7,R_4k7_5%_1/16W_0402,2,YAG1287CT-ND,0.09,4k7
R6,R_10k_5%_1/16W_0402,1,YAG1281CT-ND,0.09,10k
R8,R_200k_1%_1/16W_0402,1,13-RC0402FR-13200KLCT-ND,0.09,200k
R9/R10,R_DNP_0402,2,,,DNP
R11/R12/R13/R14,R_100k_1%_1/16W_0402,4,311-100KLRCT-ND,0.08,100k
R15,R_0R_1%_1/16W_0402,1,13-AC0402FR-070RLCT-ND,0.09,0R
SW1,switch_slide_2pos,1,1948-1089-ND,2.36,SW 0.5A 24V
SW2/SW3,EVQ-P7A01P,2,P16763CT-ND,0.26,Button 90°
SW4,TL3315NF160Q,1,EG4621CT-ND,0.13,Button
U1,LSM303AH,1,497-17053-1-ND,4.54,LSM303AHTR
U2,TCA39306DCUR,1,296-TCA39306DCURCT-ND,0.9,TCA39306DCUR
U3,BGA725L6E6327FTSA1,1,BGA725L6E6327FTSA1CT-ND,0.4,BGA725L6E6327FTSA1
U4,ST1S12GR,1,497-6906-1-ND,1.06,ST1S12GR
U5,B39162B4327P810,1,495-7424-1-ND,1.47,B39162B4327P810
U6,TESEO-LIV3R,1,497-19468-1-ND,13.36,TESEO-LIV3R
U7,74LVC1T45GW.125,1,1727-4560-1-ND,0.29,74LVC1T45GW
U8,TPS61222DCKR,1,296-39435-1-ND,1.11,TPS61222DCKR
U9,TPS79318DBVR,1,296-12155-1-ND,0.45,TPS79318DBVR
U10,RYLR998,1,-,12,RYLR998
U11,STM32L431RCT6TR,1,497-STM32L431RCT6CT-ND,4.43,STM32L431
U12,ASE-8.000MHZ-L-C-T,1,535-ASE-8.000MHZ-L-C-TCT-ND,1.17,8MHz
U13,MIC5330-SSYML-TR,1,576-1947-1-ND,1.15,MIC5330-3V3/3V3

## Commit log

2024-04-07 Setup project
2024-04-07 Edit gitignore
2024-04-07 update gitignore 2 lel
2024-05-12 Progress
2024-05-16 Remove useless backup files
2024-10-02 Add LEDs
2024-10-07 Add TP & level shifter
2024-10-09 Finish schematic minus mcu
2024-11-24 Layout start
2024-11-30 First layout draft
2025-02-22 Add TPs
2025-02-24 Start placing TPs
2025-02-24 Remove lck files
2025-02-26 Finish pcb?
2025-02-26 First order
2025-02-26 Fix MIC5330 DPN
2025-02-26 Regen BOM
2025-02-27 Replace outdated inductor
2025-03-02 Update missing paste layer
2025-03-02 Regen gerber zip
2025-03-08 Remove pcb backups
2025-03-08 Setup pins & generate code
2025-03-08 Make into release folder
2025-03-19 Add courtyard to testpoints
2025-03-22 LED files
2025-03-23 LED driver
2025-03-23 gitignore
2025-03-23 Gitignores
2025-03-23 gitignore again ffs
2025-03-30 Add printer through VCP
2025-04-25 Add lora uart RX
2025-05-18 Change lora uart rx to dma
2025-05-23 lora setup, mag_acc defines
2025-05-24 toolchain setup, lora init working
2025-05-24 Start lsm303 setup
2025-05-24 CubeMx config for teseo, move to LL mostly
2025-06-06 LEDs using LL for TIM + DMA
2025-06-07 WIP, lora TX not working?
2025-06-09 LORA working in LL
2025-06-09 Debug details
2025-06-15 LORA functional
2025-06-15 Clean ioc
2025-06-15 Rename GPIOs
2025-06-15 lora to rylr in files
2025-06-15 Add teseo
